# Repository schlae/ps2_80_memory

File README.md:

# PS/2 Model 80 1MB/2MB Memory Card Clone

IBM PS/2 Model 80 computers use a proprietary memory card instead of the more
common SIMM memory modules. I've reverse engineered a 3rd party memory board
that uses standard memory chips instead of the MST modules that the IBM
cards use. If you can't get an original card, or if the MST modules on your
card have gone bad, this project may be a good way to get your computer
back up and running.

[Schematic](ps2_80_memory.pdf)

[Fab Files](fab/ps2_80_memory-rev1.zip)

## Fabrication Notes

This is a 4-layer board. The stackup is not critical and the two inner layers
are just power and ground. The dimensions are 98.6 x 100mm. The thickness is
the standard 0.062" (1.6mm). 

## Bill of Materials

| Q  | Designator | Description       | MFG PN              | Mouser P/N         |
|----|------------|-------------------|---------------------|--------------------|
| 1  | J1         | DIN41612\_R\_3x32 | HARTING 09732966801 | 617-09-73-296-6801 |
| 26 | C1 - C26   | Cap, 0.1uF 25V 0603 | (Generic)         | |
| 2  | U1, U2     | 74F244 or AM2966PC | 74F244             | 595-SN74F244N |
| 16 | U3 - U18   | 256K x 4 DRAM, 80ns or faster | 44C256  | |
| 8  | U19 - U26  | 256K x 1 DRAM, 80ns or faster | 41C256  | |
| 1  | R1         | 0 ohm resistor, 0805 | | |
| 0  | R2         | DNI | | |
| 0  | R3         | DNI | | |

This bill of materials is for the full 2MB version of the card. For 1MB, populate as follows

| Q  | Designator | Description       | MFG PN              | Mouser P/N         |
|----|------------|-------------------|---------------------|--------------------|
| 1  | J1         | DIN41612\_R\_3x32 | HARTING 09732966801 | 617-09-73-296-6801 |
| 26 | C1 - C26   | Cap, 0.1uF 25V 0603 | (Generic)         | |
| 2  | U1, U2     | 74F244 or AM2966PC | 74F244             | 595-SN74F244N |
| 8  | U3 - U10   | 256K x 4 DRAM, 80ns or faster | 44C256  | |
| 4  | U19, U21, U23, U25 | 256K x 1 DRAM, 80ns or faster | 41C256 | |
| 2  | R1, R2     | 0 ohm resistor, 0805 | | |
| 0  | R3         | DNI | | |

## Assembly Notes

Assemble according to the bill of materials for the 1MB or 2MB version.
Besides the chips, the only other difference is jumper R2, which, when placed,
indicates to the computer that only 1MB is installed. You may want to omit
the extra bypass capacitors if you're only installing 1MB, but for flexibility,
I recommend socketing all the chips and including all the memory so it is easy
to switch back and forth.

## Troubleshooting

As with any accessory for the IBM PS/2 family of computers, troubleshooting
involves frustration and arcane knowledge. I recommend the following resources

* [IBM 8580 Common Devices](https://www.ardent-tool.com/8580/Common.html) - See the sections on memory
* [IBM 8580 Planar Memory](https://www.ardent-tool.com/8580/Memory.html)

The BIOS does some "intelligent" things, like swapping around blocks of memory,
which can make troubleshooting difficult.

## License
This work is licensed under a Creative Commons Attribution-ShareAlike 4.0
International License. See [https://creativecommons.org/licenses/by-sa/4.0/](https://creativecommons.org/licenses/by-sa/4.0/).

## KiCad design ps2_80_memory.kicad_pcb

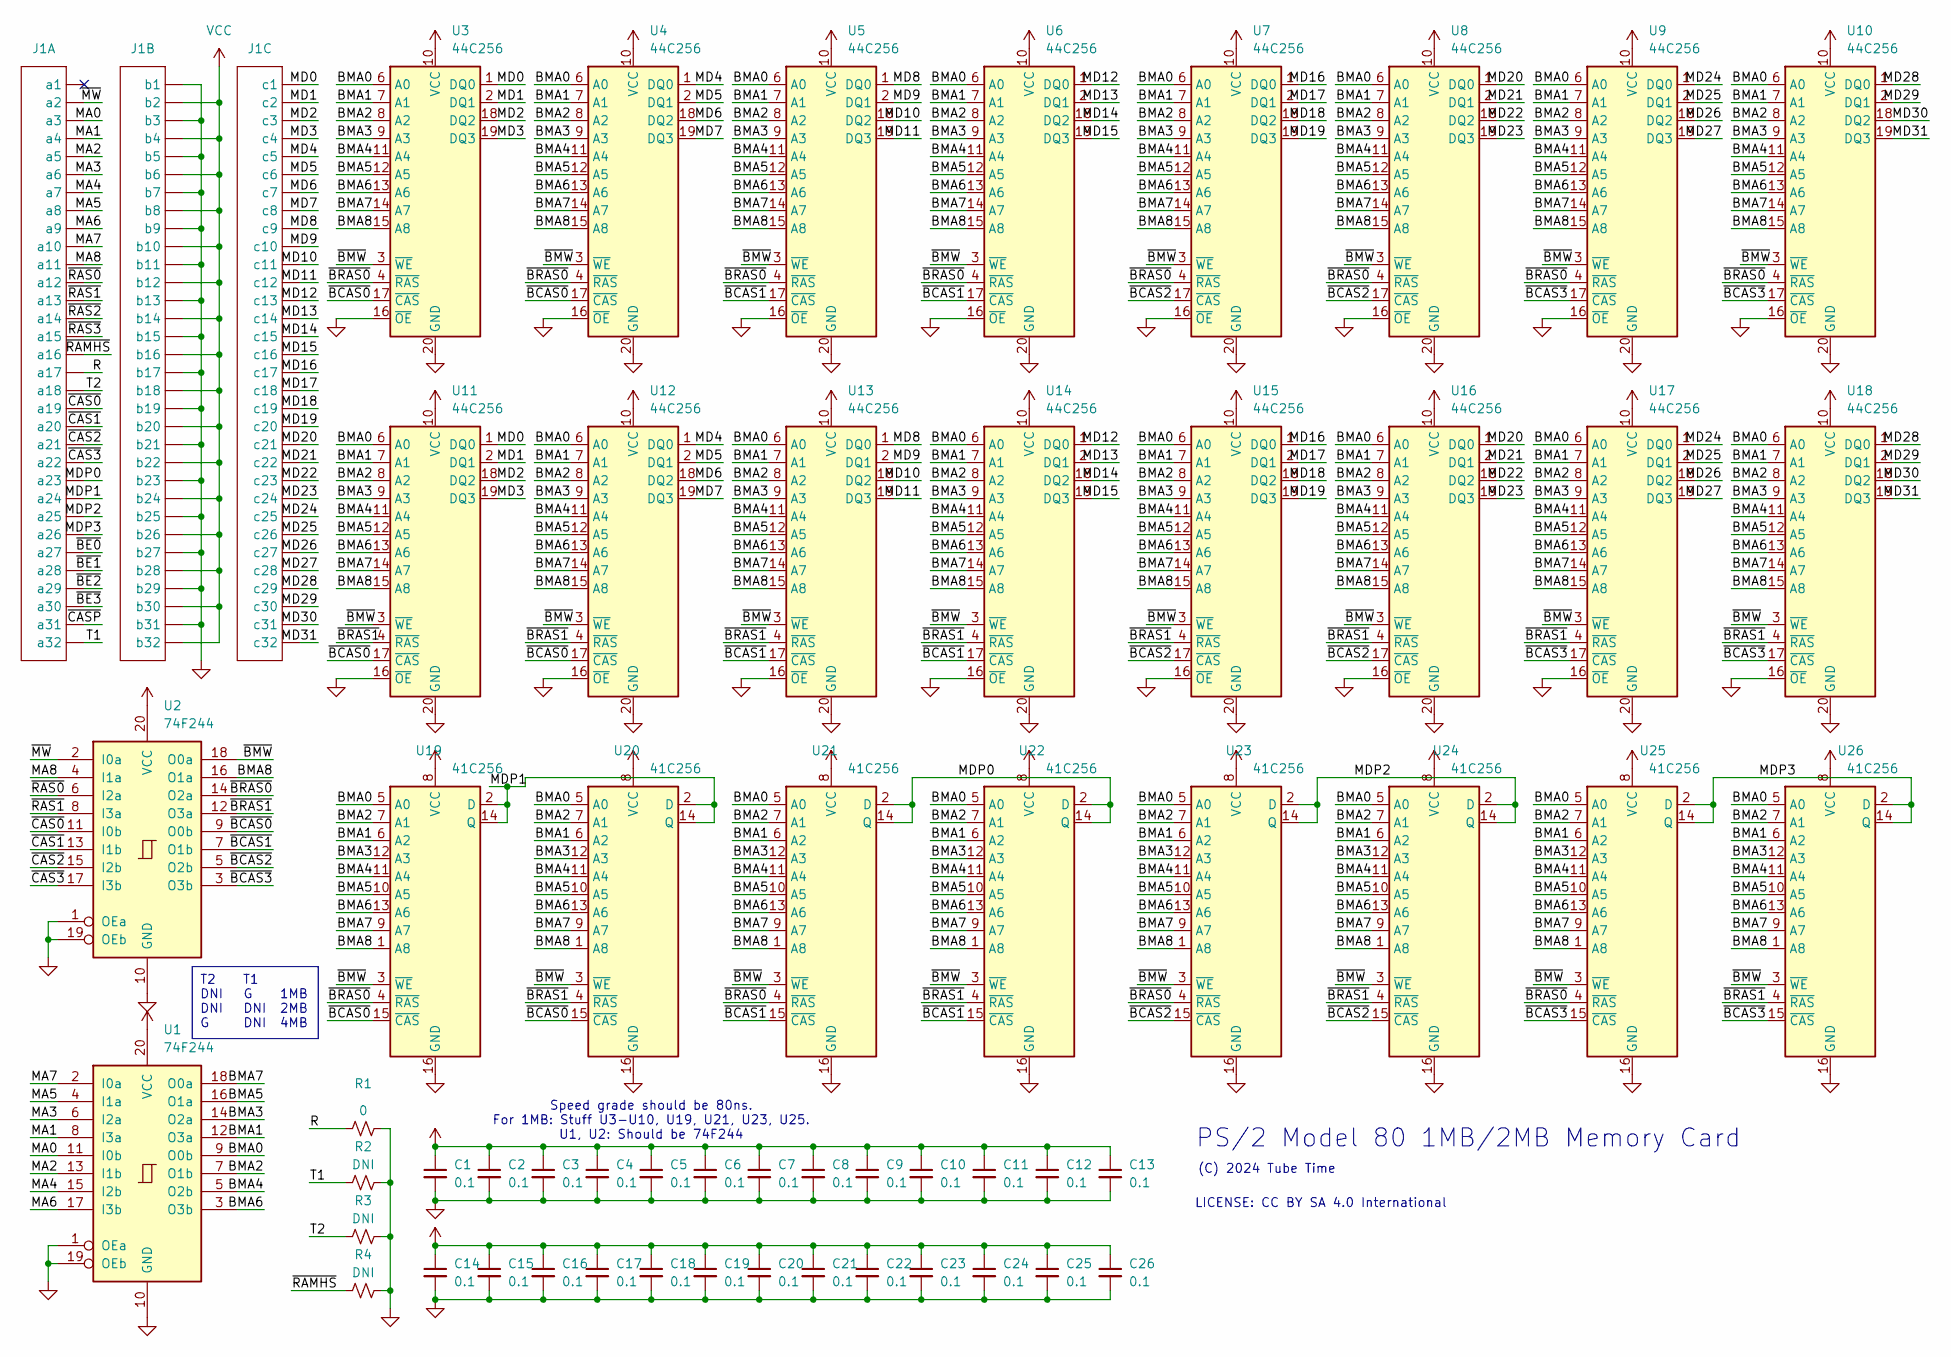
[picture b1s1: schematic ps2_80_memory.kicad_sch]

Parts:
C1, C2, C3, C4, C5, C6, C7, C8, C9, C10, C11, C12, C13, C14, C15, C16, C17, C18, C19, C20, C21, C22, C23, C24, C25, C26: 0.1; CAPC1608X100
J1: Conn_VME_3x32; DIN41612_R_3x32_Female_Horizontal_THT; Mouser 617-09-73-296-6801
R1: 0; RESC2012X55
R2, R3, R4: DNI; RESC2012X55
U1, U2: 74F244; DIP254P762X635-20
U3, U4, U5, U6, U7, U8, U9, U10, U11, U12, U13, U14, U15, U16, U17, U18: 44C256; DIP254P762X635-20
U19, U20, U21, U22, U23, U24, U25, U26: 41C256; DIP254P762X635-16

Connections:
/BMA0: U1.9 (O0b), U3.6 (A0), U4.6 (A0), U5.6 (A0), U6.6 (A0), U7.6 (A0), U8.6 (A0), U9.6 (A0), U10.6 (A0), U11.6 (A0), U12.6 (A0), U13.6 (A0), U14.6 (A0), U15.6 (A0), U16.6 (A0), U17.6 (A0), U18.6 (A0), U19.5 (A0), U20.5 (A0), U21.5 (A0), U22.5 (A0), U23.5 (A0), U24.5 (A0), U25.5 (A0), U26.5 (A0)
/BMA1: U1.12 (O3a), U3.7 (A1), U4.7 (A1), U5.7 (A1), U6.7 (A1), U7.7 (A1), U8.7 (A1), U9.7 (A1), U10.7 (A1), U11.7 (A1), U12.7 (A1), U13.7 (A1), U14.7 (A1), U15.7 (A1), U16.7 (A1), U17.7 (A1), U18.7 (A1), U19.6 (A2), U20.6 (A2), U21.6 (A2), U22.6 (A2), U23.6 (A2), U24.6 (A2), U25.6 (A2), U26.6 (A2)
/BMA2: U1.7 (O1b), U3.8 (A2), U4.8 (A2), U5.8 (A2), U6.8 (A2), U7.8 (A2), U8.8 (A2), U9.8 (A2), U10.8 (A2), U11.8 (A2), U12.8 (A2), U13.8 (A2), U14.8 (A2), U15.8 (A2), U16.8 (A2), U17.8 (A2), U18.8 (A2), U19.7 (A1), U20.7 (A1), U21.7 (A1), U22.7 (A1), U23.7 (A1), U24.7 (A1), U25.7 (A1), U26.7 (A1)
/BMA3: U1.14 (O2a), U3.9 (A3), U4.9 (A3), U5.9 (A3), U6.9 (A3), U7.9 (A3), U8.9 (A3), U9.9 (A3), U10.9 (A3), U11.9 (A3), U12.9 (A3), U13.9 (A3), U14.9 (A3), U15.9 (A3), U16.9 (A3), U17.9 (A3), U18.9 (A3), U19.12 (A3), U20.12 (A3), U21.12 (A3), U22.12 (A3), U23.12 (A3), U24.12 (A3), U25.12 (A3), U26.12 (A3)
/BMA4: U1.5 (O2b), U3.11 (A4), U4.11 (A4), U5.11 (A4), U6.11 (A4), U7.11 (A4), U8.11 (A4), U9.11 (A4), U10.11 (A4), U11.11 (A4), U12.11 (A4), U13.11 (A4), U14.11 (A4), U15.11 (A4), U16.11 (A4), U17.11 (A4), U18.11 (A4), U19.11 (A4), U20.11 (A4), U21.11 (A4), U22.11 (A4), U23.11 (A4), U24.11 (A4), U25.11 (A4), U26.11 (A4)
/BMA5: U1.16 (O1a), U3.12 (A5), U4.12 (A5), U5.12 (A5), U6.12 (A5), U7.12 (A5), U8.12 (A5), U9.12 (A5), U10.12 (A5), U11.12 (A5), U12.12 (A5), U13.12 (A5), U14.12 (A5), U15.12 (A5), U16.12 (A5), U17.12 (A5), U18.12 (A5), U19.10 (A5), U20.10 (A5), U21.10 (A5), U22.10 (A5), U23.10 (A5), U24.10 (A5), U25.10 (A5), U26.10 (A5)
/BMA6: U1.3 (O3b), U3.13 (A6), U4.13 (A6), U5.13 (A6), U6.13 (A6), U7.13 (A6), U8.13 (A6), U9.13 (A6), U10.13 (A6), U11.13 (A6), U12.13 (A6), U13.13 (A6), U14.13 (A6), U15.13 (A6), U16.13 (A6), U17.13 (A6), U18.13 (A6), U19.13 (A6), U20.13 (A6), U21.13 (A6), U22.13 (A6), U23.13 (A6), U24.13 (A6), U25.13 (A6), U26.13 (A6)
/BMA7: U1.18 (O0a), U3.14 (A7), U4.14 (A7), U5.14 (A7), U6.14 (A7), U7.14 (A7), U8.14 (A7), U9.14 (A7), U10.14 (A7), U11.14 (A7), U12.14 (A7), U13.14 (A7), U14.14 (A7), U15.14 (A7), U16.14 (A7), U17.14 (A7), U18.14 (A7), U19.9 (A7), U20.9 (A7), U21.9 (A7), U22.9 (A7), U23.9 (A7), U24.9 (A7), U25.9 (A7), U26.9 (A7)
/BMA8: U2.16 (O1a), U3.15 (A8), U4.15 (A8), U5.15 (A8), U6.15 (A8), U7.15 (A8), U8.15 (A8), U9.15 (A8), U10.15 (A8), U11.15 (A8), U12.15 (A8), U13.15 (A8), U14.15 (A8), U15.15 (A8), U16.15 (A8), U17.15 (A8), U18.15 (A8), U19.1 (A8), U20.1 (A8), U21.1 (A8), U22.1 (A8), U23.1 (A8), U24.1 (A8), U25.1 (A8), U26.1 (A8)
/MA0: J1.a3, U1.11 (I0b)
/MA1: J1.a4, U1.8 (I3a)
/MA2: J1.a5, U1.13 (I1b)
/MA3: J1.a6, U1.6 (I2a)
/MA4: J1.a7, U1.15 (I2b)
/MA5: J1.a8, U1.4 (I1a)
/MA6: J1.a9, U1.17 (I3b)
/MA7: J1.a10, U1.2 (I0a)
/MA8: J1.a11, U2.4 (I1a)
/MD0: J1.c1, U3.1 (DQ0), U11.1 (DQ0)
/MD1: J1.c2, U3.2 (DQ1), U11.2 (DQ1)
/MD2: J1.c3, U3.18 (DQ2), U11.18 (DQ2)
/MD3: J1.c4, U3.19 (DQ3), U11.19 (DQ3)
/MD4: J1.c5, U4.1 (DQ0), U12.1 (DQ0)
/MD5: J1.c6, U4.2 (DQ1), U12.2 (DQ1)
/MD6: J1.c7, U4.18 (DQ2), U12.18 (DQ2)
/MD7: J1.c8, U4.19 (DQ3), U12.19 (DQ3)
/MD8: J1.c9, U5.1 (DQ0), U13.1 (DQ0)
/MD9: J1.c10, U5.2 (DQ1), U13.2 (DQ1)
/MD10: J1.c11, U5.18 (DQ2), U13.18 (DQ2)
/MD11: J1.c12, U5.19 (DQ3), U13.19 (DQ3)
/MD12: J1.c13, U6.1 (DQ0), U14.1 (DQ0)
/MD13: J1.c14, U6.2 (DQ1), U14.2 (DQ1)
/MD14: J1.c15, U6.18 (DQ2), U14.18 (DQ2)
/MD15: J1.c16, U6.19 (DQ3), U14.19 (DQ3)
/MD16: J1.c17, U7.1 (DQ0), U15.1 (DQ0)
/MD17: J1.c18, U7.2 (DQ1), U15.2 (DQ1)
/MD18: J1.c19, U7.18 (DQ2), U15.18 (DQ2)
/MD19: J1.c20, U7.19 (DQ3), U15.19 (DQ3)
/MD20: J1.c21, U8.1 (DQ0), U16.1 (DQ0)
/MD21: J1.c22, U8.2 (DQ1), U16.2 (DQ1)
/MD22: J1.c23, U8.18 (DQ2), U16.18 (DQ2)
/MD23: J1.c24, U8.19 (DQ3), U16.19 (DQ3)
/MD24: J1.c25, U9.1 (DQ0), U17.1 (DQ0)
/MD25: J1.c26, U9.2 (DQ1), U17.2 (DQ1)
/MD26: J1.c27, U9.18 (DQ2), U17.18 (DQ2)
/MD27: J1.c28, U9.19 (DQ3), U17.19 (DQ3)
/MD28: J1.c29, U10.1 (DQ0), U18.1 (DQ0)
/MD29: J1.c30, U10.2 (DQ1), U18.2 (DQ1)
/MD30: J1.c31, U10.18 (DQ2), U18.18 (DQ2)
/MD31: J1.c32, U10.19 (DQ3), U18.19 (DQ3)
/MDP0: J1.a23, U21.2 (D), U21.14 (Q), U22.2 (D), U22.14 (Q)
/MDP1: J1.a24, U19.2 (D), U19.14 (Q), U20.2 (D), U20.14 (Q)
/MDP2: J1.a25, U23.2 (D), U23.14 (Q), U24.2 (D), U24.14 (Q)
/MDP3: J1.a26, U25.2 (D), U25.14 (Q), U26.2 (D), U26.14 (Q)
/R: J1.a17, R1.1
/T1: J1.a32, R2.1
/T2: J1.a18, R3.1
/~BCAS0: U2.9 (O0b), U3.17 (~CAS), U4.17 (~CAS), U11.17 (~CAS), U12.17 (~CAS), U19.15 (~CAS), U20.15 (~CAS)
/~BCAS1: U2.7 (O1b), U5.17 (~CAS), U6.17 (~CAS), U13.17 (~CAS), U14.17 (~CAS), U21.15 (~CAS), U22.15 (~CAS)
/~BCAS2: U2.5 (O2b), U7.17 (~CAS), U8.17 (~CAS), U15.17 (~CAS), U16.17 (~CAS), U23.15 (~CAS), U24.15 (~CAS)
/~BCAS3: U2.3 (O3b), U9.17 (~CAS), U10.17 (~CAS), U17.17 (~CAS), U18.17 (~CAS), U25.15 (~CAS), U26.15 (~CAS)
/~BE0: J1.a27
/~BE1: J1.a28
/~BE2: J1.a29
/~BE3: J1.a30
/~BMW: U2.18 (O0a), U3.3 (~WE), U4.3 (~WE), U5.3 (~WE), U6.3 (~WE), U7.3 (~WE), U8.3 (~WE), U9.3 (~WE), U10.3 (~WE), U11.3 (~WE), U12.3 (~WE), U13.3 (~WE), U14.3 (~WE), U15.3 (~WE), U16.3 (~WE), U17.3 (~WE), U18.3 (~WE), U19.3 (~WE), U20.3 (~WE), U21.3 (~WE), U22.3 (~WE), U23.3 (~WE), U24.3 (~WE), U25.3 (~WE), U26.3 (~WE)
/~BRAS0: U2.14 (O2a), U3.4 (~RAS), U4.4 (~RAS), U5.4 (~RAS), U6.4 (~RAS), U7.4 (~RAS), U8.4 (~RAS), U9.4 (~RAS), U10.4 (~RAS), U19.4 (~RAS), U21.4 (~RAS), U23.4 (~RAS), U25.4 (~RAS)
/~BRAS1: U2.12 (O3a), U11.4 (~RAS), U12.4 (~RAS), U13.4 (~RAS), U14.4 (~RAS), U15.4 (~RAS), U16.4 (~RAS), U17.4 (~RAS), U18.4 (~RAS), U20.4 (~RAS), U22.4 (~RAS), U24.4 (~RAS), U26.4 (~RAS)
/~CAS0: J1.a19, U2.11 (I0b)
/~CAS1: J1.a20, U2.13 (I1b)
/~CAS2: J1.a21, U2.15 (I2b)
/~CAS3: J1.a22, U2.17 (I3b)
/~CASP: J1.a31
/~MW: J1.a2, U2.2 (I0a)
/~RAMHS: J1.a16, R4.1
/~RAS0: J1.a12, U2.6 (I2a)
/~RAS1: J1.a13, U2.8 (I3a)
/~RAS2: J1.a14
/~RAS3: J1.a15
GND: C1.2, C2.2, C3.2, C4.2, C5.2, C6.2, C7.2, C8.2, C9.2, C10.2, C11.2, C12.2, C13.2, C14.2, C15.2, C16.2, C17.2, C18.2, C19.2, C20.2, C21.2, C22.2, C23.2, C24.2, C25.2, C26.2, J1.b1, J1.b3, J1.b5, J1.b7, J1.b9, J1.b11, J1.b13, J1.b15, J1.b17, J1.b19, J1.b21, J1.b23, J1.b25, J1.b27, J1.b29, J1.b31, R1.2, R2.2, R3.2, R4.2, U1.1 (OEa), U1.10 (GND), U1.19 (OEb), U2.1 (OEa), U2.10 (GND), U2.19 (OEb), U3.16 (~OE), U3.20 (GND), U4.16 (~OE), U4.20 (GND), U5.16 (~OE), U5.20 (GND), U6.16 (~OE), U6.20 (GND), U7.16 (~OE), U7.20 (GND), U8.16 (~OE), U8.20 (GND), U9.16 (~OE), U9.20 (GND), U10.16 (~OE), U10.20 (GND), U11.16 (~OE), U11.20 (GND), U12.16 (~OE), U12.20 (GND), U13.16 (~OE), U13.20 (GND), U14.16 (~OE), U14.20 (GND), U15.16 (~OE), U15.20 (GND), U16.16 (~OE), U16.20 (GND), U17.16 (~OE), U17.20 (GND), U18.16 (~OE), U18.20 (GND), U19.16 (GND), U20.16 (GND), U21.16 (GND), U22.16 (GND), U23.16 (GND), U24.16 (GND), U25.16 (GND), U26.16 (GND)
VCC: C1.1, C2.1, C3.1, C4.1, C5.1, C6.1, C7.1, C8.1, C9.1, C10.1, C11.1, C12.1, C13.1, C14.1, C15.1, C16.1, C17.1, C18.1, C19.1, C20.1, C21.1, C22.1, C23.1, C24.1, C25.1, C26.1, J1.b2, J1.b4, J1.b6, J1.b8, J1.b10, J1.b12, J1.b14, J1.b16, J1.b18, J1.b20, J1.b22, J1.b24, J1.b26, J1.b28, J1.b30, J1.b32, U1.20 (VCC), U2.20 (VCC), U3.10 (VCC), U4.10 (VCC), U5.10 (VCC), U6.10 (VCC), U7.10 (VCC), U8.10 (VCC), U9.10 (VCC), U10.10 (VCC), U11.10 (VCC), U12.10 (VCC), U13.10 (VCC), U14.10 (VCC), U15.10 (VCC), U16.10 (VCC), U17.10 (VCC), U18.10 (VCC), U19.8 (VCC), U20.8 (VCC), U21.8 (VCC), U22.8 (VCC), U23.8 (VCC), U24.8 (VCC), U25.8 (VCC), U26.8 (VCC)

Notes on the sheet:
T2 T1 DNI G 1MB DNI DNI 2MB G DNI 4MB
PS/2 Model 80 1MB/2MB Memory Card
Speed grade should be 80ns. For 1MB: Stuff U3-U10, U19, U21, U23, U25. U1, U2: Should be 74F244
(C) 2024 Tube Time
LICENSE: CC BY SA 4.0 International

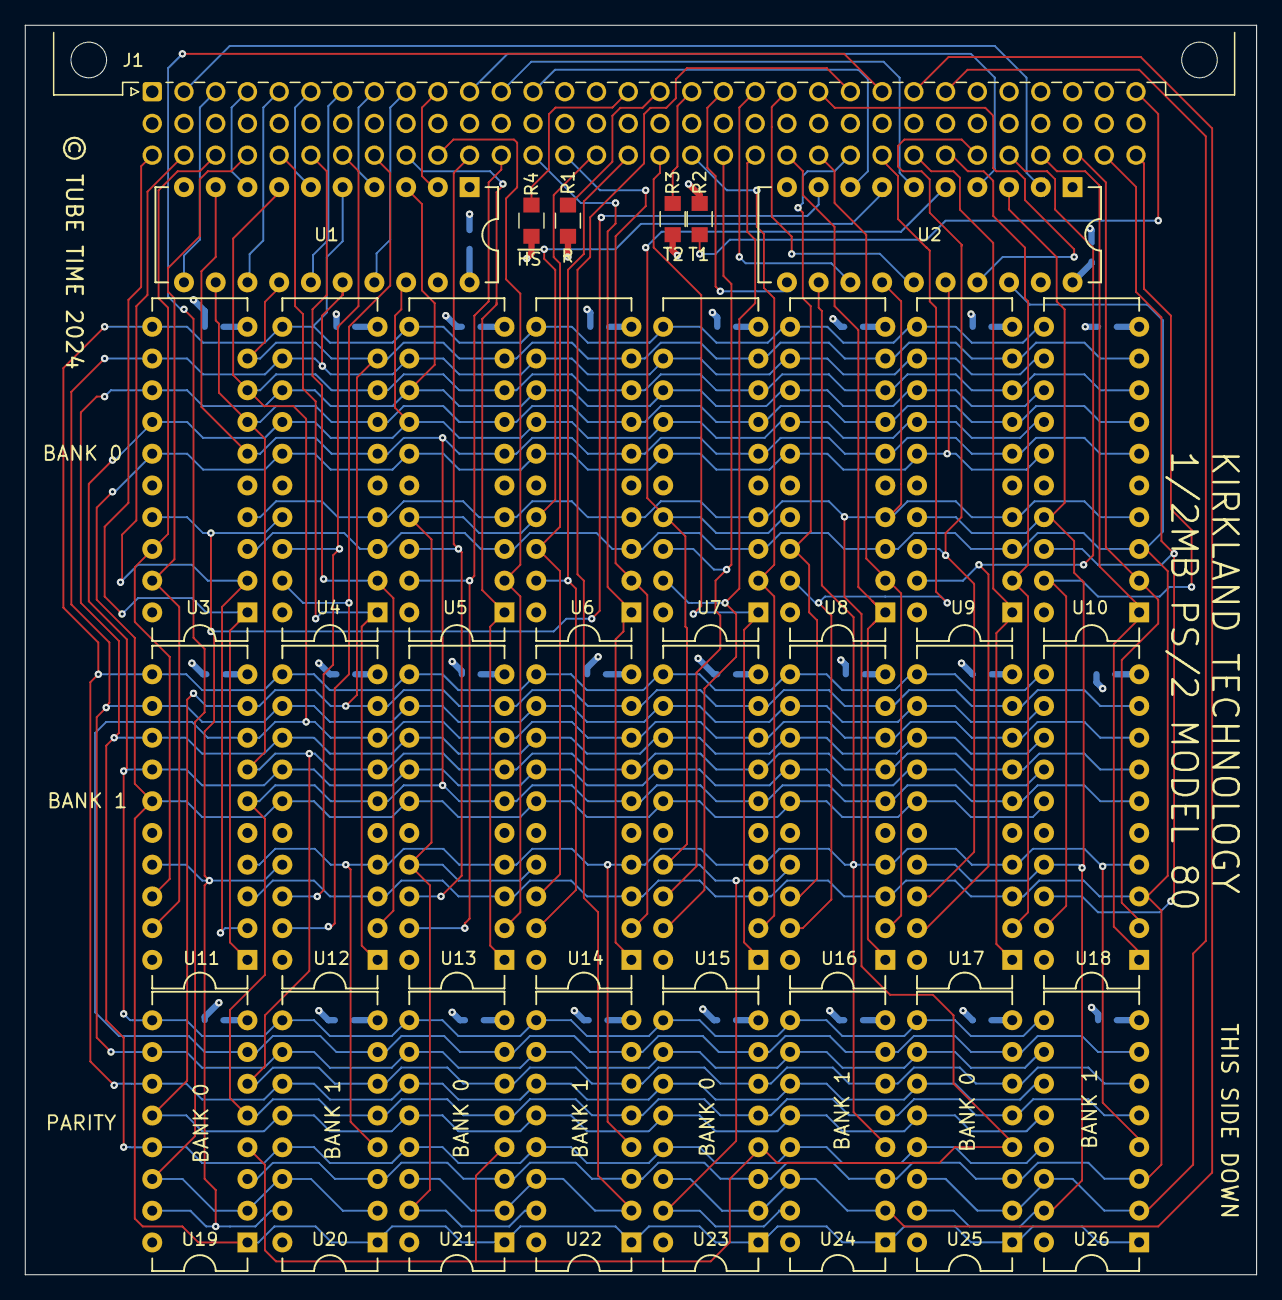
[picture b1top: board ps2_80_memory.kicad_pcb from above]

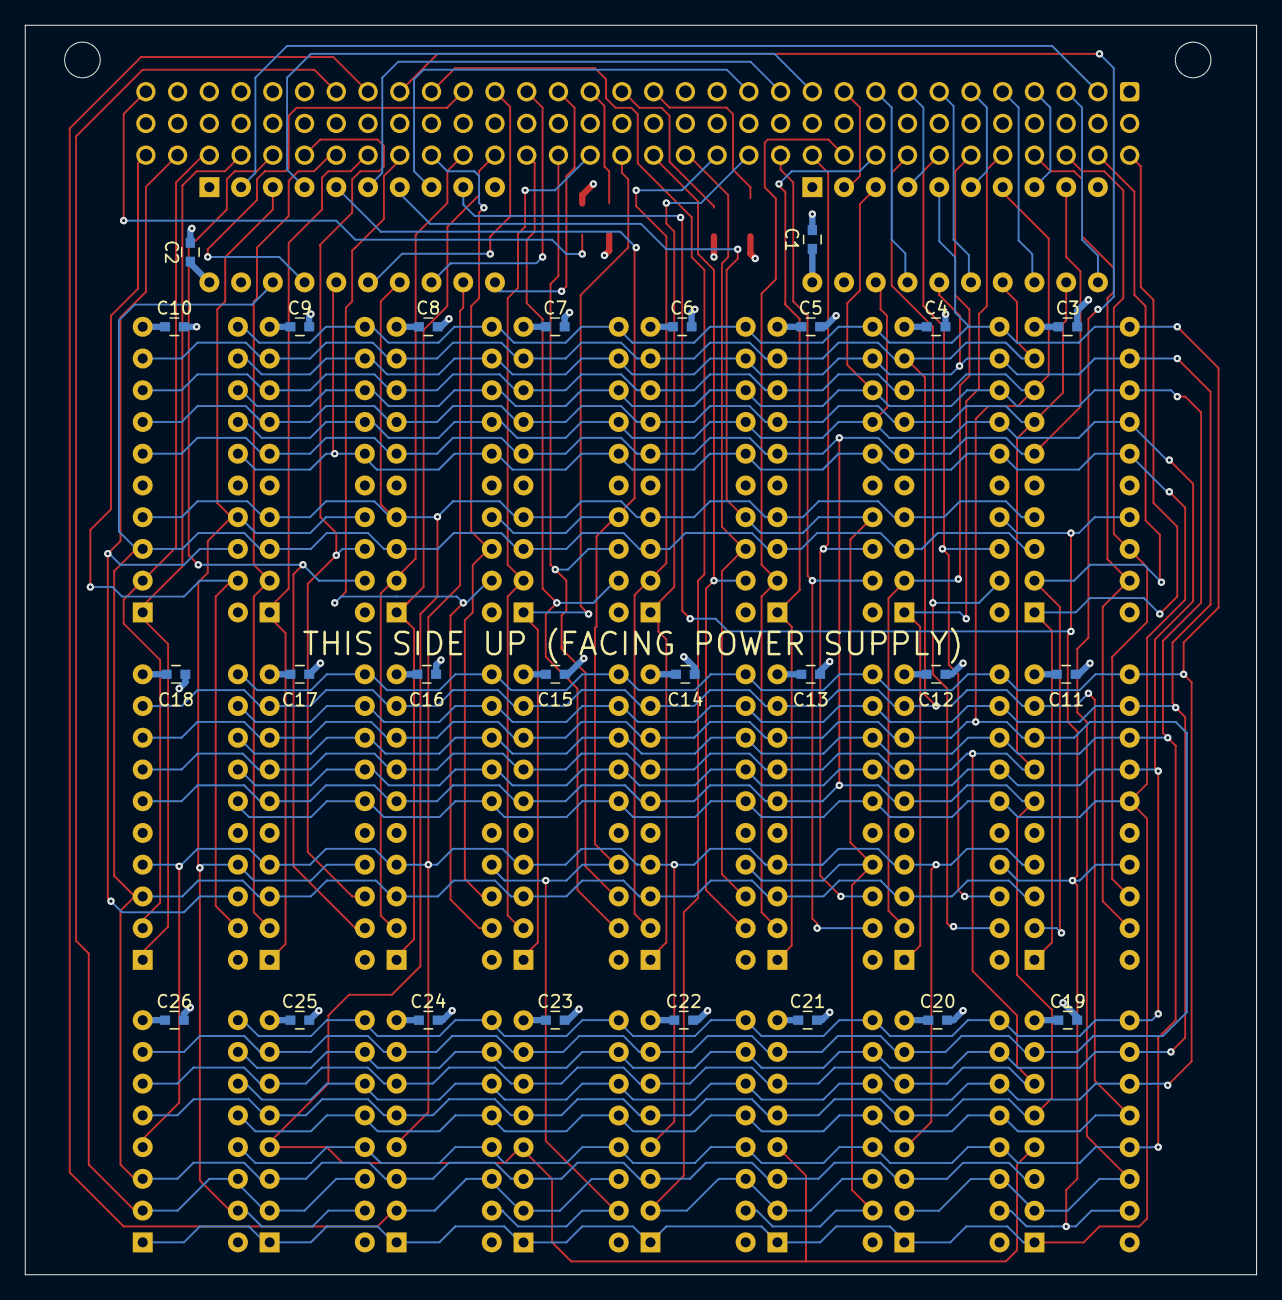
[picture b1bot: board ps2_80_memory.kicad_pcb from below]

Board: 4 copper layers, 98.6 x 100.0 mm, 57 parts (26 on the bottom side), 74 nets.

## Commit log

2024-11-21 Initial version
2024-11-21 Add license

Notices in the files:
ps2_80_memory.kicad_pcb:
© TUBE TIME 2024
